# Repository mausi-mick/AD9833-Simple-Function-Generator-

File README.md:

AD9833-Simple-Function-Generator

The project based on the project "Signal Generator AD9833" from Peter Balch :
    •  https://www.instructables.com/Signal-Generator-AD9833/
    • where the input commands like Curve-Type (Sine, Triangle, Square) , Sweep or Frequency are send from a PC via USB to Arduino-Nano and from there to the AD9833 Signalgenerator-Modul.
    • I changed the program  so that it works standalone without connection to the PC.
    • For input the commands, I use only a rotary encoder with integrated push-button-switch.
    • A HD44780 display (LCD1602) shows all information (Curve-Type, Frequency, sweep ...)
    • On the encoder I use external interrupts (Pin2 / Pin3 Arduino NANO) , on push-button-switch I use Pin-Change-Interrupt (PCI) for a direct/quick response.
    • A small Video is here:   https://www.youtube.com/watch?v=DLXJh2jmxDk
    • or here: video  („TRIANGLE“) :   https://www.youtube.com/watch?v=seZB-FUj7es
    • In the new version I have expand the program with new functions inside the AD9833-Signal-Generator and outside this function with a digital ConstantCurrentSource (CCS) working from about 1µA ( starts at 10 µA ) to 4095 µA (step 1 µA) or from 10 µA to 40.95 mA (step 10 µA) .
    • I have expand now the device (and program) with a second sine-generator (AD9850) module,
    • so you have two independent siganl-sources.

So the device  includes now this functions:

    • AD9833 Signalgenerator for Sine, Triangle and Squarewave up to 12.5 Mhz in 1 Hz-Steps 
      
    • digital ConstantCurrentSource/Sink from 10 µA to 4.095 mA (Stepwidth : 1 µA) or (10 µA to 40.95 mA with stepwidth 10 µA) 
    • Low-Frequency Function-Generator for Sinus, Triangle StepUp , StepDown and Squarewave for low frequencies (mHz to some kHz) 
    • optionally : AD9850  Sine-genarator  (second siganl-source)
    • 
For small budget I use only a few parts with price over 1 $/€:

    • AD9833 board
    • AD9850 board (optional)
    • HD44780 with I2C 
    • Arduino NANO (clone?) 
    • DAC MCP4822 
    • OPV MCP6002 
    • n-Mosfet BSP89  (high Voltage, low Idss)
    • Rotary Encoder with push-button 
    • n-Mosfet for switching Rp ( from 1025 Ohm to 10.25 Ohm) with Low R-on (< 100 mOhm) 
    • 5V Zener/Ref-Diode  (or other stabilization for MCP4822/MCP6002) 
    • 2x MT3608 Step up (5V/ for NANO/LCD..., 28V for CurrentSource) 
    • Battery-holder for 18650 Battery 
    • USB  Lion-loader board 
    • 18650 Lion-Battery (one piece) 
    • 
More information in the next days.

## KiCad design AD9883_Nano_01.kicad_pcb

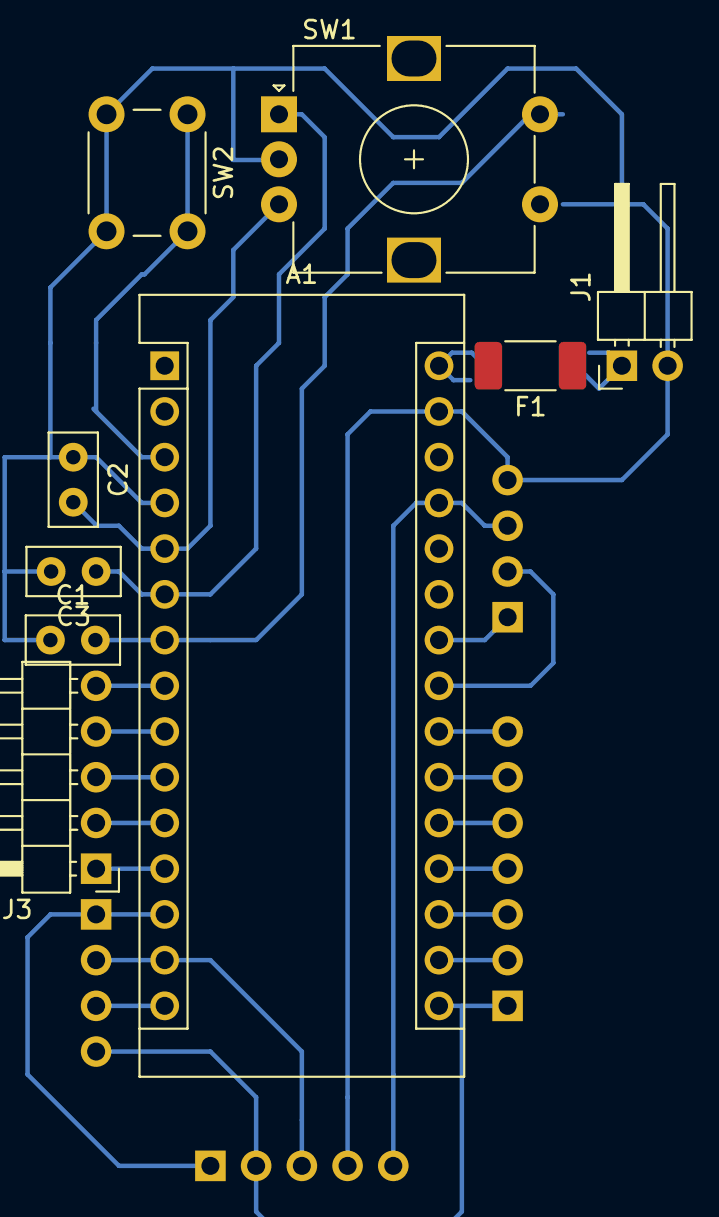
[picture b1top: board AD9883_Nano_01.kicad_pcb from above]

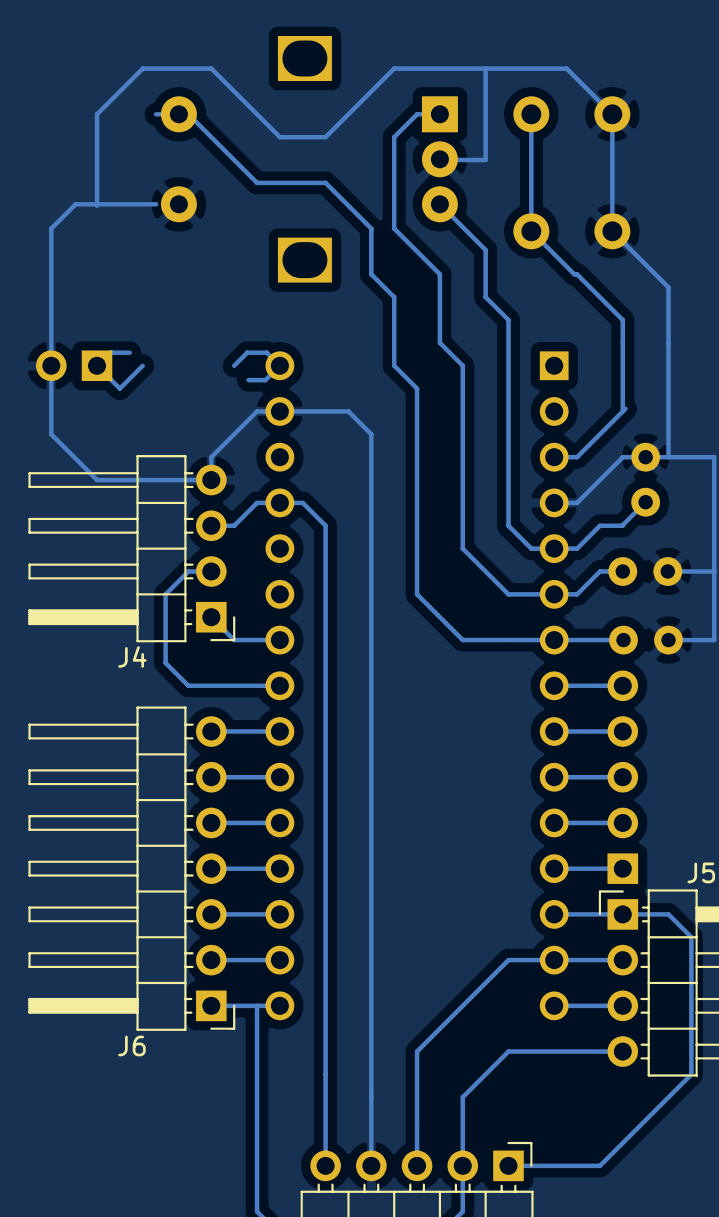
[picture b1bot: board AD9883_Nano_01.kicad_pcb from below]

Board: 2 copper layers, 13 parts (4 on the bottom side), 25 nets.

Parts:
A1: Arduino_Nano_v3.x; Arduino_Nano
C1, C2, C3: 10nF; C_Disc_D5.0mm_W2.5mm_P2.50mm
F1: Fuse_Small 500mA; Fuse_2010_5025Metric_Pad1.52x2.65mm_HandSolder
J1: Conn_Power_7_12V; PinHeader_1x02_P2.54mm_Horizontal
J2: Conn_to_AD9833; PinHeader_1x05_P2.54mm_Horizontal
J3: Conn_open; PinHeader_1x05_P2.54mm_Horizontal
J4: Conn_to_I2C_LCD; PinHeader_1x04_P2.54mm_Horizontal
J5: Conn_SPI; PinHeader_1x04_P2.54mm_Horizontal
J6: Conn_ADC; PinHeader_1x07_P2.54mm_Horizontal
SW1: Rotary_Encoder_Switch; RotaryEncoder_Alps_EC12E-Switch_Vertical_H20mm
SW2: SW_DIP_x01; SW_PUSH_6mm_H7.3mm

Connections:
+5V: A1.27, J2.5, J4.3
+9V: F1.1, J1.1
GND: A1.4, A1.29, C1.1, C2.1, C3.2, J1.2, J2.4, J4.4, SW1.C, SW1.S2, SW2.2
unnamed: A1.3, SW2.1
unnamed: A1.5, C2.2, SW1.B
unnamed: A1.6, C3.1, SW1.A
unnamed: A1.7, C1.2, SW1.S1
unnamed: A1.8, J3.5
unnamed: A1.9, J3.4
unnamed: A1.10, J3.3
unnamed: A1.11, J3.2
unnamed: A1.12, J3.1
unnamed: A1.13, J2.1, J5.1
unnamed: A1.14, J2.3, J5.2
unnamed: A1.15, J5.3
unnamed: A1.16, J2.2, J5.4, J6.1
unnamed: A1.17, J6.2
unnamed: A1.18, J6.3
unnamed: A1.19, J6.4
unnamed: A1.20, J6.5
unnamed: A1.21, J6.6
unnamed: A1.22, J6.7
unnamed: A1.23, J4.2
unnamed: A1.24, J4.1
unnamed: A1.30, F1.2
